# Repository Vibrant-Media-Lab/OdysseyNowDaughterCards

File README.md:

# Odyssey Now Daughter Cards

Replacement daughter card schematics and layouts for the Magnavox Odyssey BLAK version.

## Layout
* `OdysseyDaughterCard<name>` (KiCad 8 project)
  * `3D_models/` (WRL and STEP files for the board)
  * `footprints/` (non-standard footprint libraries for project)
  * `gerbers/` (last generated gerbers for layout)
  * `images/` (a render of the board)
  * `pdf/` (pdfs of schematic and layout)
  * `symbols/` (non-standard symbol libraries for project)
  * `dimensions.txt` (board dimension in meters for easier ordering from places like AllPCB)

## Bill of Materials
* See OdysseyDaughtCardsBillOfMaterials.xlsx for a list components used in the last round of boards made in the VML.

## License
* Designed by Levi Burner and Zachary Horton
* Each card's design is available under Creative Commons Attribution. All license text must be included in any redistribution and attribution must be given to original design and designers. See LICENSE.txt in each card's folder for additional details.

## Old Designs (legacy)
The original git history for each card (including old prototypes that were made and are likely to be floating around in the VML) be found on the `legacy-*` branches.

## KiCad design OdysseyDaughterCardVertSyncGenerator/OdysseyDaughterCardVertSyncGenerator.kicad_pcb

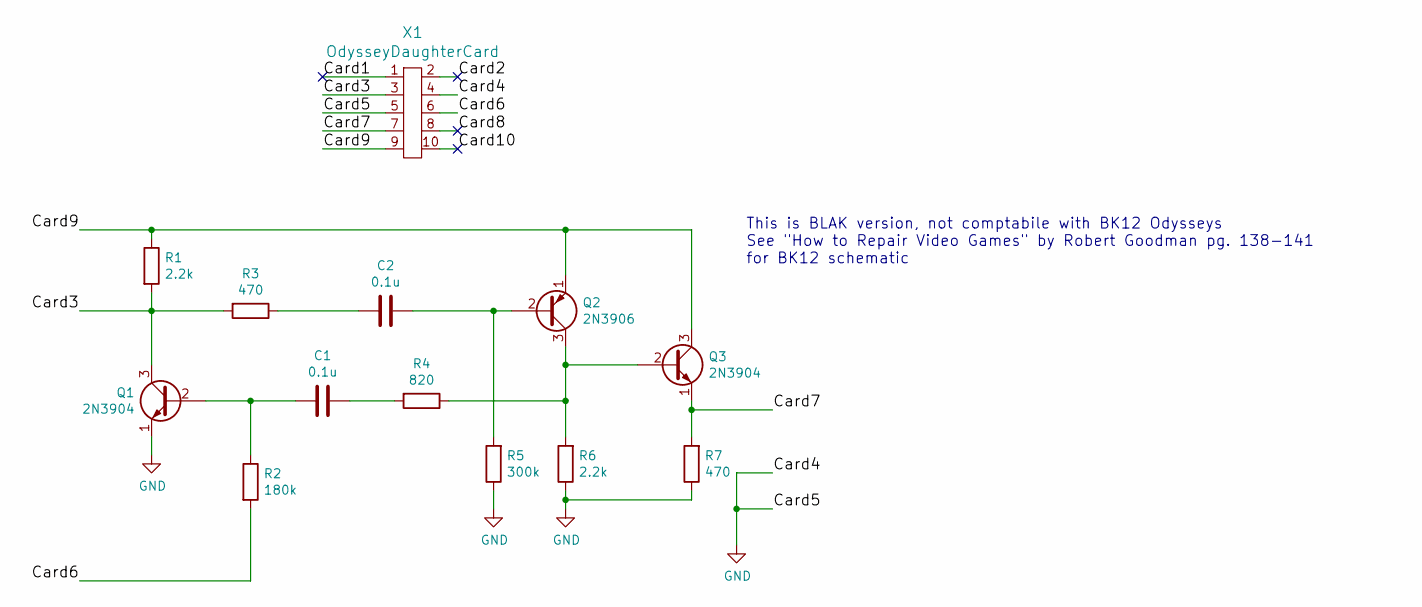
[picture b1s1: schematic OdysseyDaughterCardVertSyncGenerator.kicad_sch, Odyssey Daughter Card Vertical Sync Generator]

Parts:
C1, C2: 0.1u; C_Disc_D5.1mm_W3.2mm_P5.00mm
Q1, Q3: 2N3904; TO-92_Inline_Wide
Q2: 2N3906; TO-92_Inline_Wide
R1, R6: 2.2k; R_Axial_DIN0207_L6.3mm_D2.5mm_P7.62mm_Horizontal
R2: 180k; R_Axial_DIN0207_L6.3mm_D2.5mm_P7.62mm_Horizontal
R3, R7: 470; R_Axial_DIN0207_L6.3mm_D2.5mm_P7.62mm_Horizontal
R4: 820; R_Axial_DIN0207_L6.3mm_D2.5mm_P7.62mm_Horizontal
R5: 300k; R_Axial_DIN0207_L6.3mm_D2.5mm_P7.62mm_Horizontal
X1: OdysseyDaughterCard; Odyssey_Daughter_Card

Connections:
/Card1: X1.1
/Card2: X1.2
/Card3: Q1.3 (C), R1.2, R3.2, X1.3
/Card6: R2.2, X1.6
/Card7: Q3.1 (E), R7.2, X1.7
/Card8: X1.8
/Card9: Q2.1 (E), Q3.3 (C), R1.1, X1.9
/Card10: X1.10
GND: Q1.1 (E), R5.1, R6.1, R7.1, X1.4, X1.5
unnamed: C1.1, R4.2
unnamed: C2.2, R3.1
unnamed: C1.2, Q1.2 (B), R2.1
unnamed: C2.1, Q2.2 (B), R5.2
unnamed: Q2.3 (C), Q3.2 (B), R4.1, R6.2

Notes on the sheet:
This is BLAK version, not comptabile with BK12 Odysseys See "How to Repair Video Games" by Robert Goodman pg. 138-141 for BK12 schematic

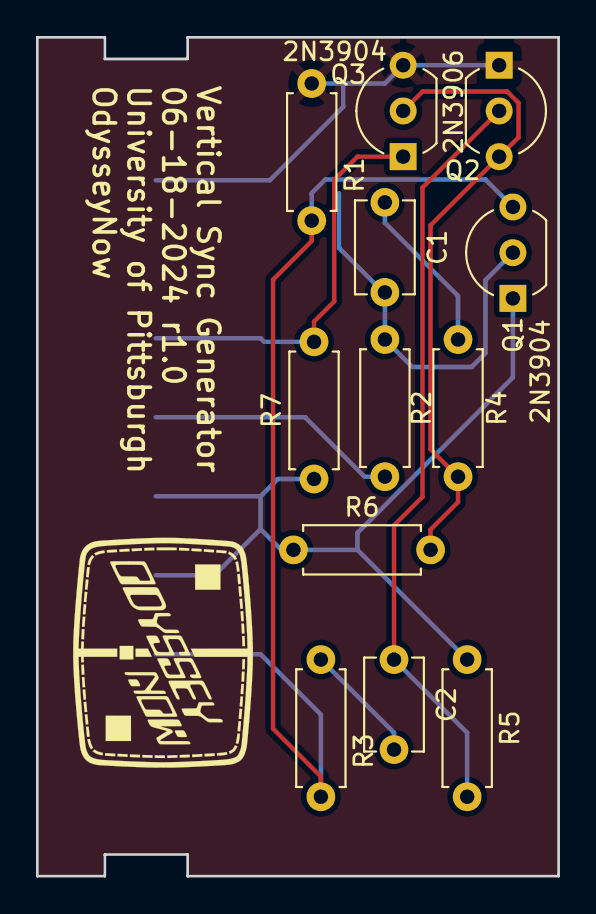
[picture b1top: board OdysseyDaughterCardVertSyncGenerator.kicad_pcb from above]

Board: 2 copper layers, 29.0 x 46.6 mm, 14 parts (0 on the bottom side), 10 nets.

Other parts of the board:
X2: OdysseyNow_Logo; OdysseyNowLogo

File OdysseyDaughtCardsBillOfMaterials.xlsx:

|  |  |  |  |  | # Parts | 19 | 12 | 15 | 19 | 15 | 11
 |  |  |  |  |  | Non PCB Cost Per Unit (10pcs) | 1.6139999999999999 | 2.2650000000000001 | 1.635 | 2.0720000000000001 | 2.0720000000000001 | 1.175
 |  |  |  |  |  | Non PCB Cost Per Unit (100pcs) | 0.8073999999999999 | 1.1888999999999998 | 0.79349999999999987 | 1.0053000000000001 | 1.0926 | 0.54569999999999996
Type | Value | P/N | Link | Notes | CPU (10pcs) | CPU (100pcs) (prices are from 2019) | Flip Flop | Gate Matrix | Horiz Sync Generator | Spot Gen | Summer | Vert Sync Generator
Capacitor | 0.01u | BC2662CT-ND | https://www.digikey.com/product-detail/en/vishay-bc-componen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 |  | 0.11799999999999999 | 5.9900000000000002E-2 |  |  |  | 1
Capacitor | 0.15u | 445-173584-1-ND | https://www.digikey.com/product-detail/en/tdk-corporation/FG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 |  | 0.18 | 0.1021 |  |  |  | 1
Capacitor | 0.1u | BC2665CT-ND | https://www.digikey.com/product-detail/en/vishay-bc-componen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 |  | 0.16 | 8.09E-2 | 2 |  |  | 1 |  | 2
Capacitor | 100p | BC2657CT-ND | https://www.digikey.com/product-detail/en/vishay-bc-componen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 |  | 0.122 | 6.2100000000000002E-2 | 2
Capacitor | 100u | 399-6602-ND | https://www.digikey.com/product-detail/en/kemet/ESK107M6R3AC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 |  | 0.114 | 5.3400000000000003E-2 |  |  | 1
Capacitor | 10u | 399-6597-ND | https://www.digikey.com/product-detail/en/kemet/ESK106M016AC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 |  | 0.105 | 4.9299999999999997E-2 |  |  | 1
Capacitor | 120p | BC2669CT-ND | https://www.digikey.com/product-detail/en/vishay-bc-componen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 |  | 0.12 | 6.08E-2 |  |  |  | 1
Capacitor | 1500p | 445-173589-1-ND | https://www.digikey.com/product-detail/en/tdk-corporation/FG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 |  | 0.18 | 0.1021 |  |  |  | 1
Capacitor | 470p | BC2681CT-ND | https://www.digikey.com/product-detail/en/vishay-bc-componen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 |  | 0.12 | 6.08E-2 |  |  | 1
Capacitor | 680p | BC2690CT-ND | https://www.digikey.com/product-detail/en/vishay-bc-componen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 |  | 0.123 | 6.25E-2 |  |  | 1
Diode | 1N4448 | 1N4448FS-ND | https://www.digikey.com/product-detail/en/on-semiconductor/1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 |  | 8.6999999999999994E-2 | 4.7300000000000002E-2 |  | 3 |  | 2 | 8
Diode | BAT83S | BAT83S-TRGICT-ND | https://www.digikey.com/product-detail/en/vishay-semiconduct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 |  | 0.314 | 0.16639999999999999 |  | 6 |  |  | 4
Inductor | 620uH 9 Ohm | RLB0608-681KL-ND | https://www.digikey.com/product-detail/en/bourns-inc/RLB0608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 |  | 0.314 | 0.16639999999999999 |  |  | 1
Resistor | 470 | CF14JT470RCT-ND | https://www.digikey.com/product-detail/en/stackpole-electron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 |  | 0.04 | 1.6199999999999999E-2 |  |  | 1 |  |  | 2
Resistor | 820 | CF14JT820RCT-ND | https://www.digikey.com/product-detail/en/stackpole-electron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 |  | 0.04 | 1.6199999999999999E-2 |  |  | 1 |  | 1 | 1
Resistor | 100k | CF14JT100KCT-ND | https://www.digikey.com/product-detail/en/stackpole-electron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 |  | 0.04 | 1.6199999999999999E-2 |  |  |  | 1
Resistor | 10k | CF14JT10K0CT-ND | https://www.digikey.com/product-detail/en/stackpole-electron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 |  | 0.04 | 1.6199999999999999E-2 |  |  |  | 5
Resistor | 150k | CF14JT150KCT-ND | https://www.digikey.com/product-detail/en/stackpole-electron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 |  | 0.04 | 1.6199999999999999E-2 |  |  | 1
Resistor | 180k | CF14JT180KCT-ND | https://www.digikey.com/products/en?keywords=CF14JT180KCT-ND |  | 0.04 | 1.6199999999999999E-2 |  |  |  |  |  | 1
Resistor | 18k | CF14JT18K0CT-ND | https://www.digikey.com/product-detail/en/stackpole-electron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 |  | 0.04 | 1.6199999999999999E-2 |  |  |  |  | 1
Resistor | 1k | CF14JT1K00CT-ND | https://www.digikey.com/product-detail/en/stackpole-electron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 |  | 0.04 | 1.6199999999999999E-2 | 2 |  | 2
Resistor | 2.2k | CF14JT2K20CT-ND | https://www.digikey.com/product-detail/en/stackpole-electron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 |  | 0.04 | 1.6199999999999999E-2 | 1 |  |  | 1 |  | 1
Resistor | 270k | CF14JT270KCT-ND | https://www.digikey.com/product-detail/en/stackpole-electron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 |  | 0.04 | 1.6199999999999999E-2 |  |  |  | 1
Resistor | 27k | CF14JT27K0CT-ND | https://www.digikey.com/product-detail/en/stackpole-electron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 |  | 0.04 | 1.6199999999999999E-2 |  |  |  |  | 1
Resistor | 3.3k | CF14JT3K30CT-ND | https://www.digikey.com/product-detail/en/stackpole-electron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 |  | 0.04 | 1.6199999999999999E-2 |  |  | 1
Resistor | 300k | CF14JT300KCT-ND | https://www.digikey.com/product-detail/en/stackpole-electron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 |  | 0.04 | 1.6199999999999999E-2 |  |  | 1 |  |  | 1
Resistor | 4.7k | CF14JT4K70CT-ND | https://www.digikey.com/product-detail/en/stackpole-electron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 |  | 0.04 | 1.6199999999999999E-2 |  | 3
Resistor | 47k | CF14JT47K0CT-ND | https://www.digikey.com/product-detail/en/stackpole-electron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 |  | 0.04 | 1.6199999999999999E-2 | 4
Switch/Button | Slide Switch SPDT Through Hole, Right Angle | CKN9559-ND | https://www.digikey.com/product-detail/en/c-k/OS102011MA1QN1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 |  |  |  | 4
Transistor | 2N3904 | 2N3904FS-ND | https://www.digikey.com/product-detail/en/on-semiconductor/2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 |  | 0.21 | 9.1600000000000001E-2 |  |  | 1 | 3 |  | 2
Transistor | 2N3906 | 2N3906TARFSCT-ND | https://www.digikey.com/product-detail/en/on-semiconductor/2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 |  | 0.19500000000000001 | 0.10349999999999999 | 2 |  |  |  |  | 1
Transistor | BC547B | BC547BTACT-ND | https://www.digikey.com/product-detail/en/on-semiconductor/B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 |  | 0.18099999999999999 | 9.6199999999999994E-2 |  |  | 1
Transistor | BC547C | BC547CBU-ND | https://www.digikey.com/product-detail/en/on-semiconductor/B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 |  | 0.19 | 0.10050000000000001 | 2 |  |  | 1
Transistor | BC556B | BC556BTACT-ND | https://www.digikey.com/product-detail/en/on-semiconductor/B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 |  | 0.188 | 9.9900000000000003E-2 |  |  | 1

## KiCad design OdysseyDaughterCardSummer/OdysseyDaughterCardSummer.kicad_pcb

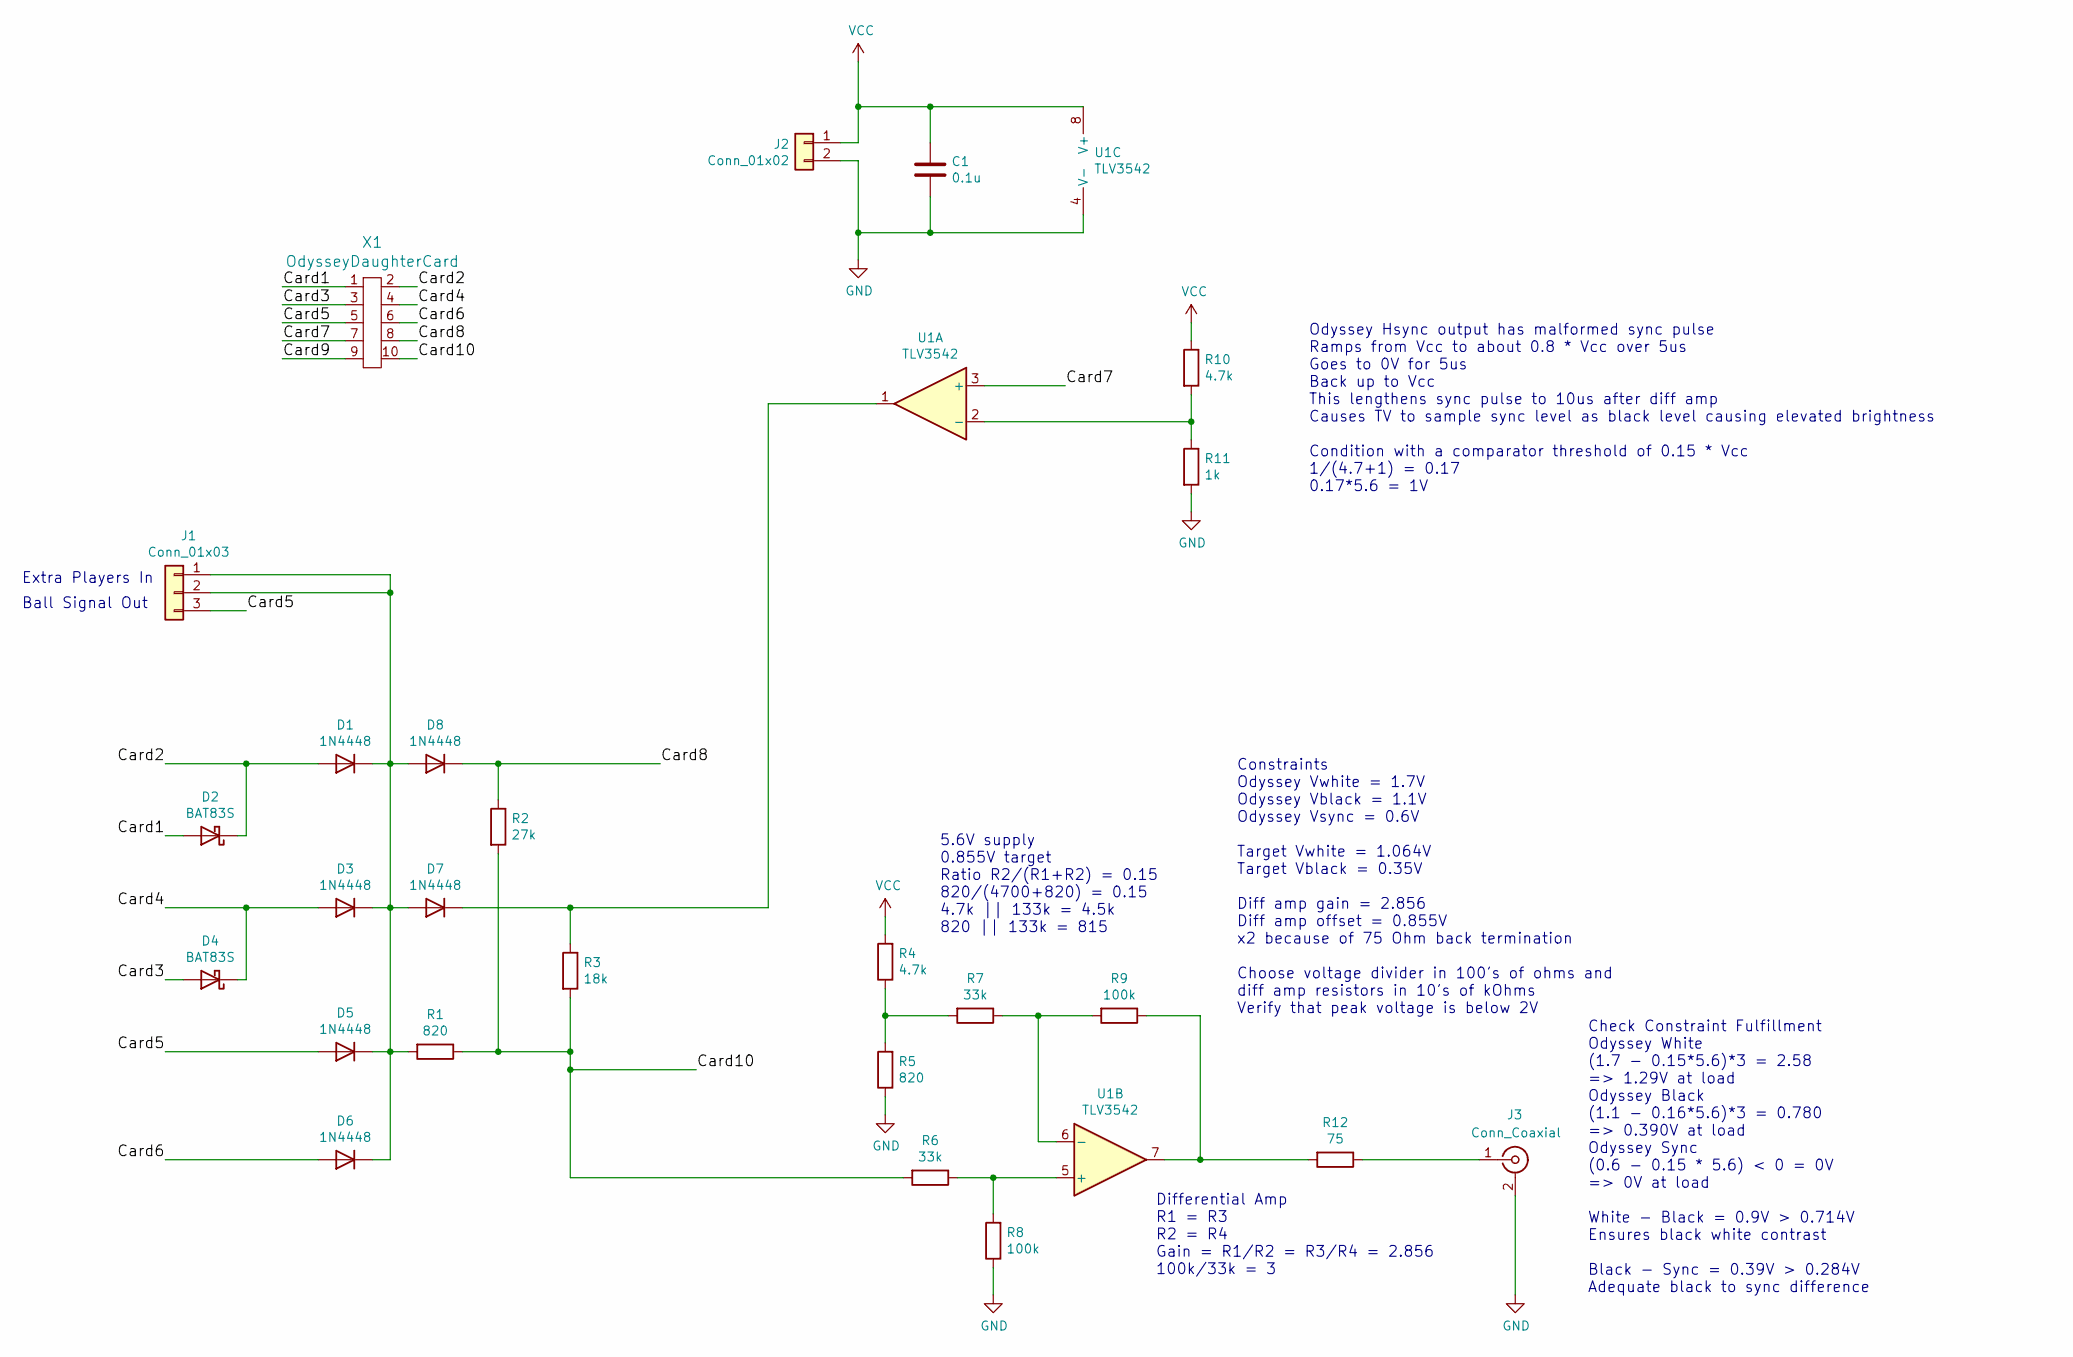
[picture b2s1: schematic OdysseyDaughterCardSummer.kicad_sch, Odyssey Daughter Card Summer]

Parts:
C1: 0.1u; C_Disc_D3.8mm_W2.6mm_P2.50mm
D1, D3, D5, D6, D7, D8: 1N4448; D_DO-35_SOD27_P7.62mm_Horizontal
D2, D4: BAT83S; D_DO-35_SOD27_P7.62mm_Horizontal
J1: Conn_01x03; PinHeader_1x03_P2.54mm_Vertical
J2: Conn_01x02; PinHeader_1x02_P2.54mm_Vertical
J3: Conn_Coaxial; PinHeader_1x02_P2.54mm_Vertical
R1, R5: 820; R_Axial_DIN0207_L6.3mm_D2.5mm_P7.62mm_Horizontal
R2: 27k; R_Axial_DIN0207_L6.3mm_D2.5mm_P7.62mm_Horizontal
R3: 18k; R_Axial_DIN0207_L6.3mm_D2.5mm_P7.62mm_Horizontal
R4, R10: 4.7k; R_Axial_DIN0207_L6.3mm_D2.5mm_P7.62mm_Horizontal
R6, R7: 33k; R_Axial_DIN0207_L6.3mm_D2.5mm_P7.62mm_Horizontal
R8, R9: 100k; R_Axial_DIN0207_L6.3mm_D2.5mm_P7.62mm_Horizontal
R11: 1k; R_Axial_DIN0207_L6.3mm_D2.5mm_P7.62mm_Horizontal
R12: 75; R_Axial_DIN0207_L6.3mm_D2.5mm_P7.62mm_Horizontal
U1: TLV3542; SOIC-8_3.9x4.9mm_P1.27mm
X1: OdysseyDaughterCard; Odyssey_Daughter_Card

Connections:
/Card1: D2.2 (A), X1.1
/Card2: D1.2 (A), D2.1 (K), X1.2
/Card3: D4.2 (A), X1.3
/Card4: D3.2 (A), D4.1 (K), X1.4
/Card5: D5.2 (A), J1.3, X1.5
/Card6: D6.2 (A), X1.6
/Card7: U1.3 (+), X1.7
/Card8: D8.1 (K), R2.1, X1.8
/Card9: X1.9
/Card10: R1.1, R2.2, R3.2, R6.2, X1.10
GND: C1.2, J2.2, J3.2 (Ext), R5.1, R8.1, R11.2, U1.4 (V-)
unnamed: D1.1 (K), D3.1 (K), D5.1 (K), D6.1 (K), D7.2 (A), D8.2 (A), J1.1, J1.2, R1.2
unnamed: D7.1 (K), R3.1, U1.1
unnamed: J3.1 (In), R12.1
unnamed: R4.1, R5.2, R7.2
unnamed: R9.1, R12.2, U1.7
unnamed: R10.2, R11.1, U1.2 (-)
unnamed: R6.1, R8.2, U1.5 (+)
unnamed: R7.1, R9.2, U1.6 (-)
VCC: C1.1, J2.1, R4.2, R10.1, U1.8 (V+)

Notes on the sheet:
Odyssey Hsync output has malformed sync pulse Ramps from Vcc to about 0.8 * Vcc over 5us Goes to 0V for 5us Back up to Vcc This lengthens sync pulse to 10us after diff amp Causes TV to sample sync level as black level causing elevated brightness Condition with a comparator threshold of 0.15 * Vcc 1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
Check Constraint Fulfillment Odyssey White (1.7 - 0.15*5.6)*3 = 2.58 => 1.29V at load Odyssey Black (1.1 - 0.16*5.6)*3 = 0.780 => 0.390V at load Odyssey Sync (0.6 - 0.15 * 5.6) < 0 = 0V => 0V at load White - Black = 0.9V > 0.714V Ensures black white contrast Black - Sync = 0.39V > 0.284V Adequate b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
Differential Amp R1 = R3 R2 = R4 Gain = R1/R2 = R3/R4 = 2.856 100k/33k = 3
Constraints Odyssey Vwhite = 1.7V Odyssey Vblack = 1.1V Odyssey Vsync = 0.6V Target Vwhite = 1.064V Target Vblack = 0.35V Diff amp gain = 2.856 Diff amp offset = 0.855V x2 because of 75 Ohm back termination Choose voltage divider in 100's of ohms and diff amp resistors in 10's of kOhms Verify that 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
5.6V supply 0.855V target Ratio R2/(R1+R2) = 0.15 820/(4700+820) = 0.15 4.7k || 133k = 4.5k 820 || 133k = 815
Extra Players In
Ball Signal Out

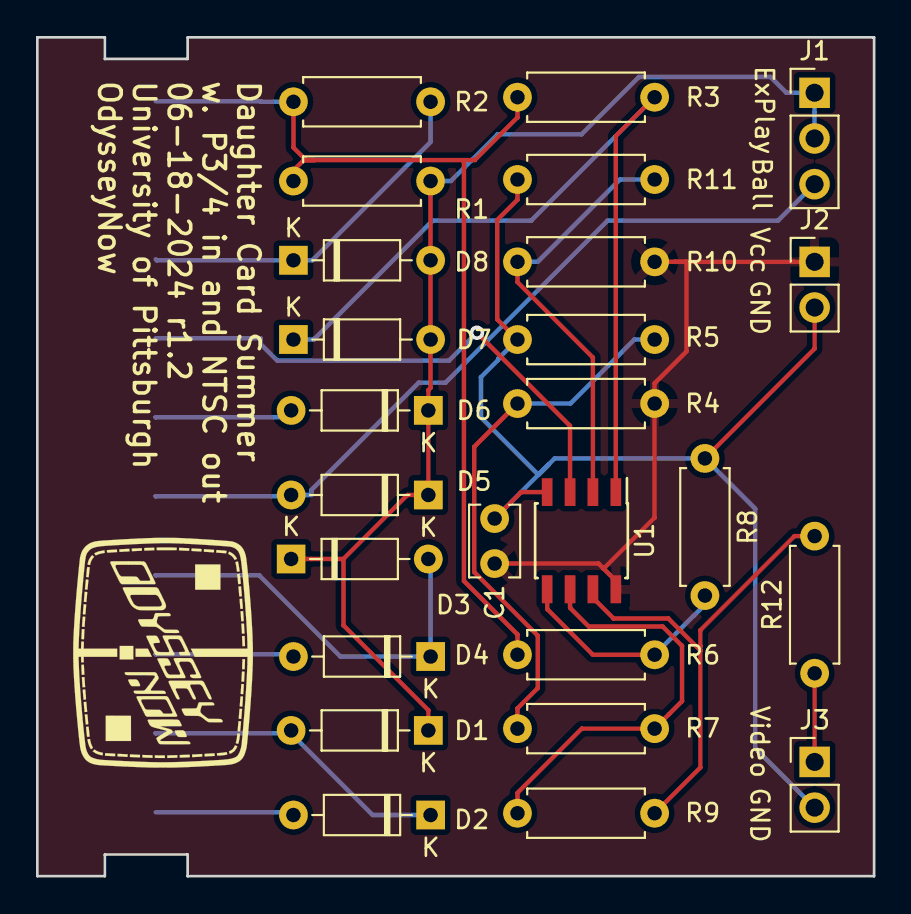
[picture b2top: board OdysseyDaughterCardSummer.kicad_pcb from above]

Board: 2 copper layers, 46.5 x 46.6 mm, 27 parts (0 on the bottom side), 19 nets.

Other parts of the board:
X2: OdysseyNow_Logo; OdysseyNowLogo

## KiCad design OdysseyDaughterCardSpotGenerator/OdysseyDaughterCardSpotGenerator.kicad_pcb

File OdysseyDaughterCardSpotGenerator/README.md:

# Odyssey Restoration Project Card Template

This is a KiCad template for an Odyssey Daughter Card.

## Revisions

### 0.1 5-29-18
Initial Version

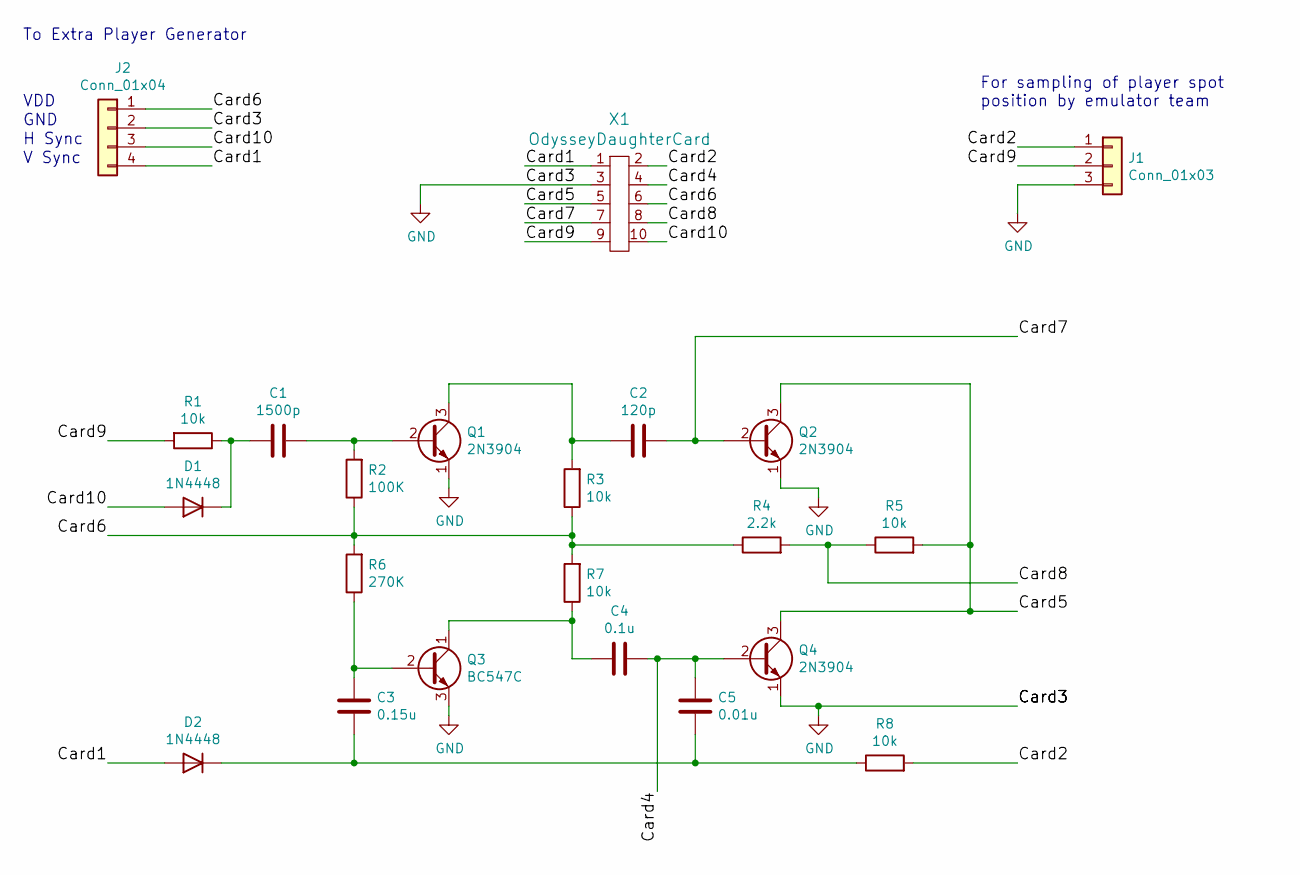
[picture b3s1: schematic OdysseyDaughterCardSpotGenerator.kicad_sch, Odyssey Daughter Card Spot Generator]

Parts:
C1: 1500p; C_Rect_L4.0mm_W2.5mm_P2.50mm
C2: 120p; C_Rect_L4.0mm_W2.5mm_P2.50mm
C3: 0.15u; C_Rect_L4.6mm_W5.5mm_P2.50mm_MKS02_FKP02
C4: 0.1u; C_Rect_L4.0mm_W2.5mm_P2.50mm
C5: 0.01u; C_Rect_L4.0mm_W2.5mm_P2.50mm
D1, D2: 1N4448; D_DO-35_SOD27_P7.62mm_Horizontal
J1: Conn_01x03; PinHeader_1x03_P2.54mm_Vertical
J2: Conn_01x04; PinHeader_1x04_P2.54mm_Vertical
Q1, Q2, Q4: 2N3904; TO-92_Inline_Wide
Q3: BC547C; TO-92_Inline_Wide
R1, R3, R5, R7, R8: 10k; R_Axial_DIN0207_L6.3mm_D2.5mm_P7.62mm_Horizontal
R2: 100K; R_Axial_DIN0207_L6.3mm_D2.5mm_P7.62mm_Horizontal
R4: 2.2k; R_Axial_DIN0207_L6.3mm_D2.5mm_P7.62mm_Horizontal
R6: 270K; R_Axial_DIN0207_L6.3mm_D2.5mm_P7.62mm_Horizontal
X1: OdysseyDaughterCard; Odyssey_Daughter_Card

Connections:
/Card1: D2.2 (A), J2.4, X1.1
/Card2: J1.1, R8.2, X1.2
/Card4: C4.2, C5.1, Q4.2 (B), X1.4
/Card5: Q2.3 (C), Q4.3 (C), R5.2, X1.5
/Card6: J2.1, R2.1, R3.1, R4.1, R6.2, R7.2, X1.6
/Card7: C2.1, Q2.2 (B), X1.7
/Card8: R4.2, R5.1, X1.8
/Card9: J1.2, R1.2, X1.9
/Card10: D1.2 (A), J2.3, X1.10
GND: J1.3, J2.2, Q1.1 (E), Q2.1 (E), Q3.3 (E), Q4.1 (E), X1.3
unnamed: C1.2, D1.1 (K), R1.1
unnamed: C3.1, C5.2, D2.1 (K), R8.1
unnamed: C1.1, Q1.2 (B), R2.2
unnamed: C2.2, Q1.3 (C), R3.2
unnamed: C3.2, Q3.2 (B), R6.1
unnamed: C4.1, Q3.1 (C), R7.1

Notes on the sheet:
VDD
For sampling of player spot position by emulator team
H Sync
GND
To Extra Player Generator
V Sync

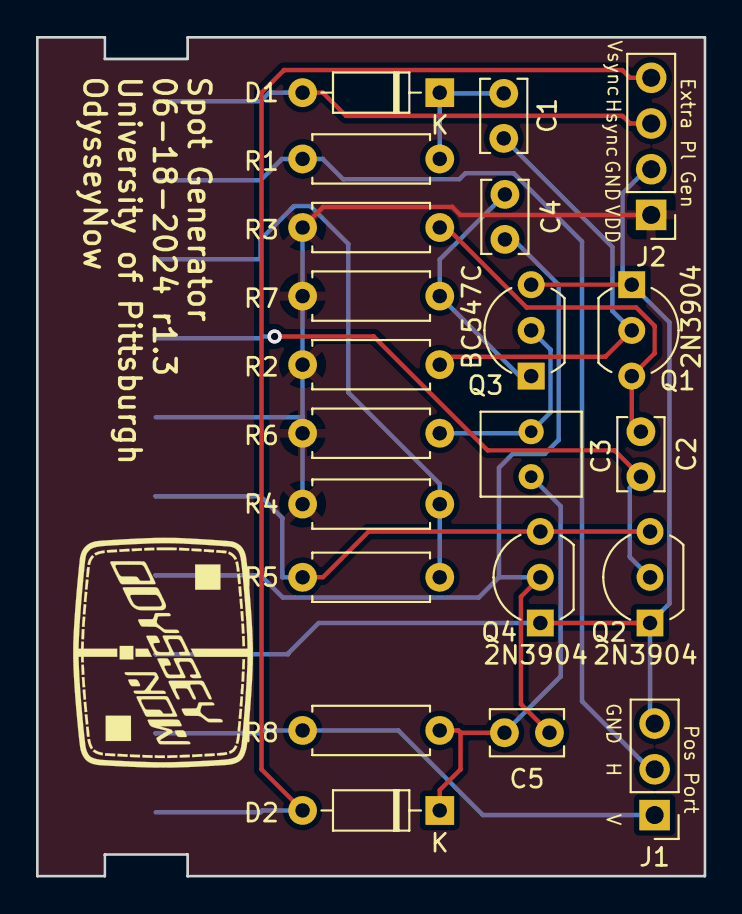
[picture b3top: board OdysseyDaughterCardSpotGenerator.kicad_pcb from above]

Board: 2 copper layers, 37.1 x 46.6 mm, 23 parts (0 on the bottom side), 16 nets.

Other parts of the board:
X2: OdysseyNow_Logo; OdysseyNowLogo

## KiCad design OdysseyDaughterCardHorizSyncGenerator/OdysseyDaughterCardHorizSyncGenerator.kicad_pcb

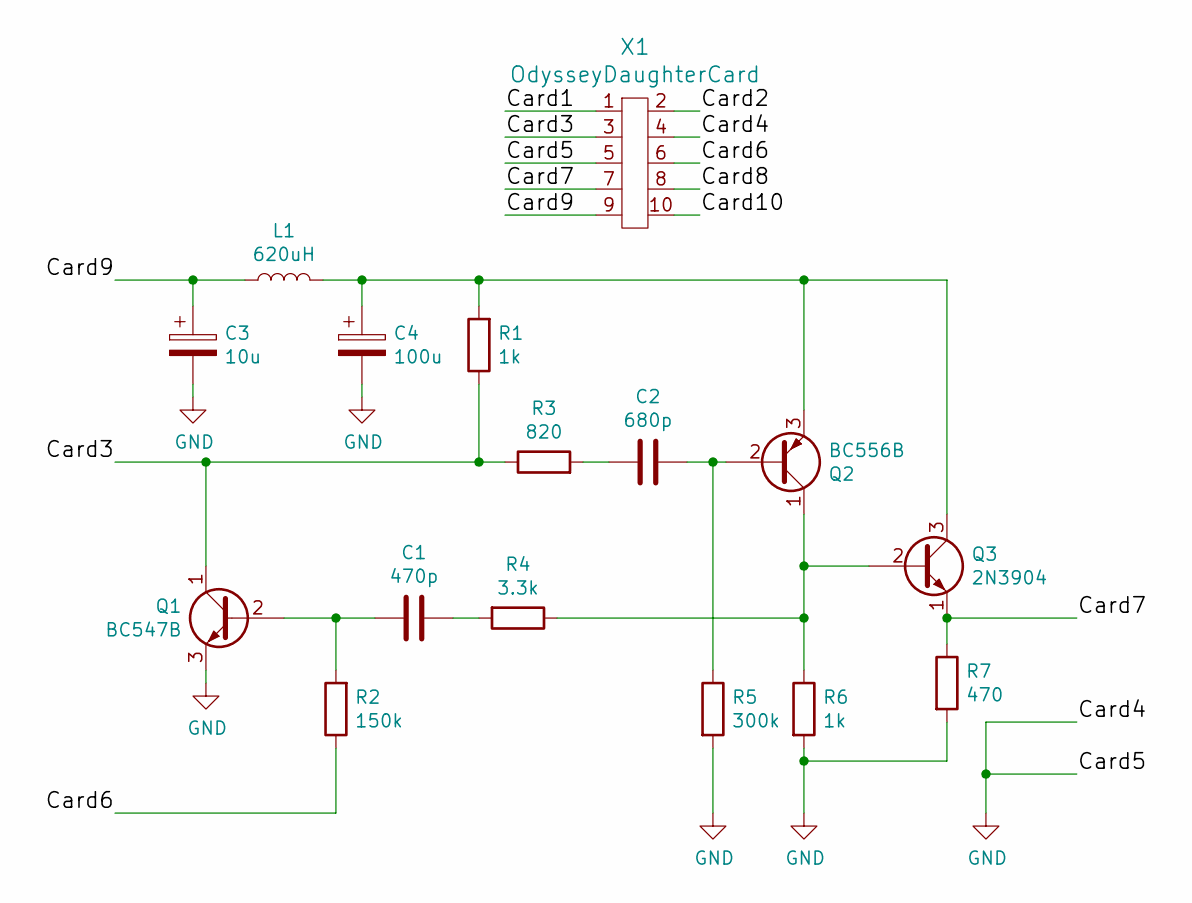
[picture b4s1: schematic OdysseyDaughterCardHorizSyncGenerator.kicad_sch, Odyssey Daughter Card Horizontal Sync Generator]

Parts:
C1: 470p; C_Disc_D5.1mm_W3.2mm_P5.00mm
C2: 680p; C_Disc_D5.1mm_W3.2mm_P5.00mm
C3: 10u; CP_Radial_D5.0mm_P2.00mm
C4: 100u; CP_Radial_D5.0mm_P2.00mm
L1: 620uH; L_Radial_D7.0mm_P3.00mm
Q1: BC547B; TO-92_Inline_Wide
Q2: BC556B; TO-92_Inline_Wide
Q3: 2N3904; TO-92_Inline_Wide
R1, R6: 1k; R_Axial_DIN0207_L6.3mm_D2.5mm_P7.62mm_Horizontal
R2: 150k; R_Axial_DIN0207_L6.3mm_D2.5mm_P7.62mm_Horizontal
R3: 820; R_Axial_DIN0207_L6.3mm_D2.5mm_P7.62mm_Horizontal
R4: 3.3k; R_Axial_DIN0207_L6.3mm_D2.5mm_P7.62mm_Horizontal
R5: 300k; R_Axial_DIN0207_L6.3mm_D2.5mm_P7.62mm_Horizontal
R7: 470; R_Axial_DIN0207_L6.3mm_D2.5mm_P7.62mm_Horizontal
X1: OdysseyDaughterCard; Odyssey_Daughter_Card

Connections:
/Card1: X1.1
/Card2: X1.2
/Card3: Q1.1 (C), R1.1, R3.1, X1.3
/Card6: R2.1, X1.6
/Card7: Q3.1 (E), R7.1, X1.7
/Card8: X1.8
/Card9: C3.1, L1.1, X1.9
/Card10: X1.10
GND: C3.2, C4.2, Q1.3 (E), R5.2, R6.2, R7.2, X1.4, X1.5
unnamed: C1.1, R4.2
unnamed: C2.2, R3.2
unnamed: C1.2, Q1.2 (B), R2.2
unnamed: C2.1, Q2.2 (B), R5.1
unnamed: Q2.1 (C), Q3.2 (B), R4.1, R6.1
unnamed: C4.1, L1.2, Q2.3 (E), Q3.3 (C), R1.2

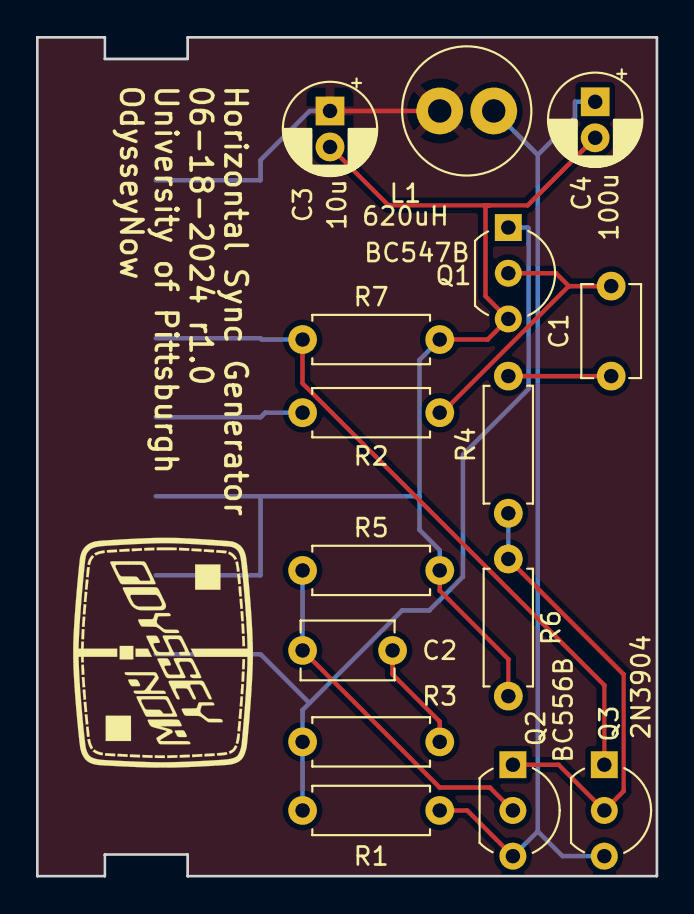
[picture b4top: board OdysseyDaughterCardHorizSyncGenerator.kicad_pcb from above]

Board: 2 copper layers, 34.4 x 46.6 mm, 17 parts (0 on the bottom side), 11 nets.

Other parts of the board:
X1#2: OdysseyNow_Logo; OdysseyNowLogo

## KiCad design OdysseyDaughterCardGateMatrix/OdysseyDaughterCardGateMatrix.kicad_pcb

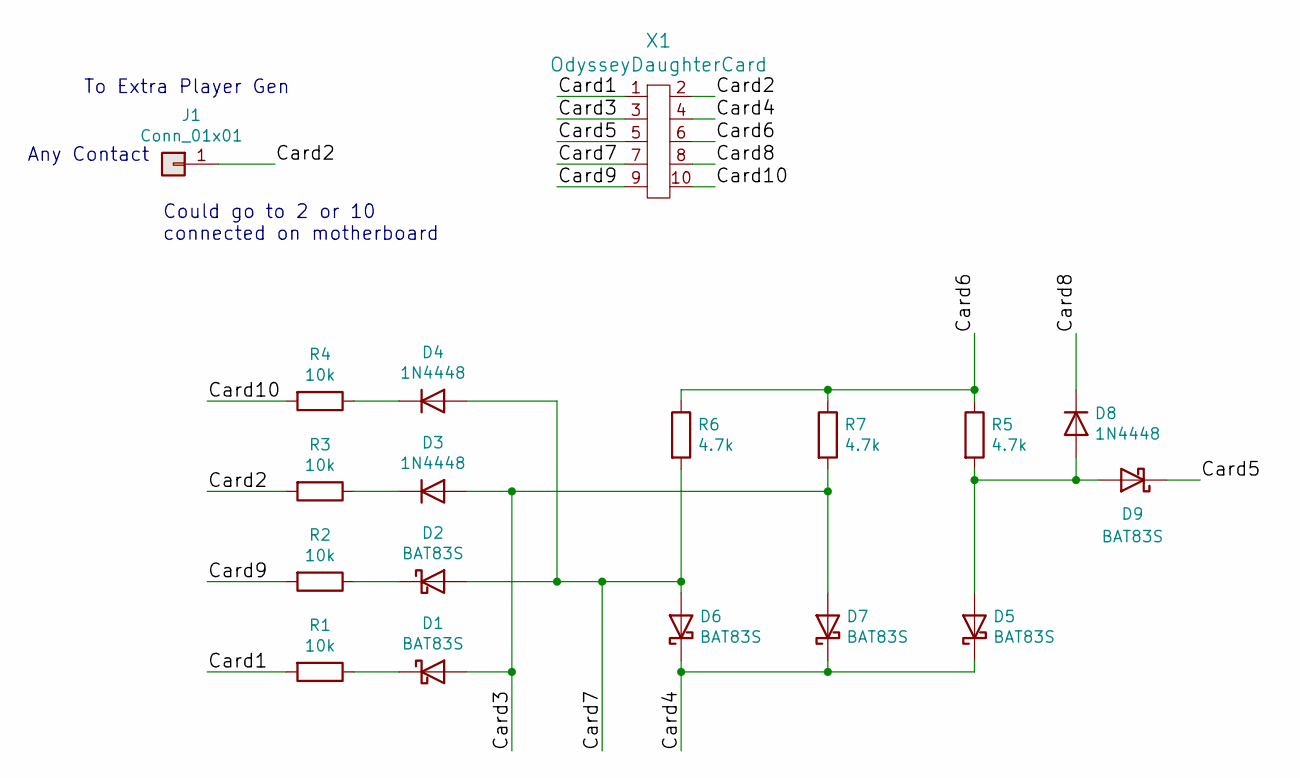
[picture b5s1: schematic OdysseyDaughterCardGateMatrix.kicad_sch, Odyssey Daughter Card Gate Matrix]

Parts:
D1, D2, D5, D6, D7, D9: BAT83S; D_DO-41_SOD81_P7.62mm_Horizontal
D3, D4, D8: 1N4448; D_DO-35_SOD27_P7.62mm_Horizontal
J1: Conn_01x01; PinHeader_1x01_P2.54mm_Vertical
R1, R2, R3, R4: 10k; R_Axial_DIN0207_L6.3mm_D2.5mm_P7.62mm_Horizontal
R5, R6, R7: 4.7k; R_Axial_DIN0207_L6.3mm_D2.5mm_P7.62mm_Horizontal
X1: OdysseyDaughterCard; Odyssey_Daughter_Card

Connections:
/Card1: R1.2, X1.1
/Card2: J1.1, R3.2, X1.2
/Card3: D1.2 (A), D3.2 (A), D7.2 (A), R7.2, X1.3
/Card4: D5.1 (K), D6.1 (K), D7.1 (K), X1.4
/Card5: D9.1 (K), X1.5
/Card6: R5.1, R6.1, R7.1, X1.6
/Card7: D2.2 (A), D4.2 (A), D6.2 (A), R6.2, X1.7
/Card8: D8.1 (K), X1.8
/Card9: R2.2, X1.9
/Card10: R4.2, X1.10
unnamed: D1.1 (K), R1.1
unnamed: D2.1 (K), R2.1
unnamed: D3.1 (K), R3.1
unnamed: D4.1 (K), R4.1
unnamed: D5.2 (A), D8.2 (A), D9.2 (A), R5.2

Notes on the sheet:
Could go to 2 or 10 connected on motherboard
To Extra Player Gen
Any Contact

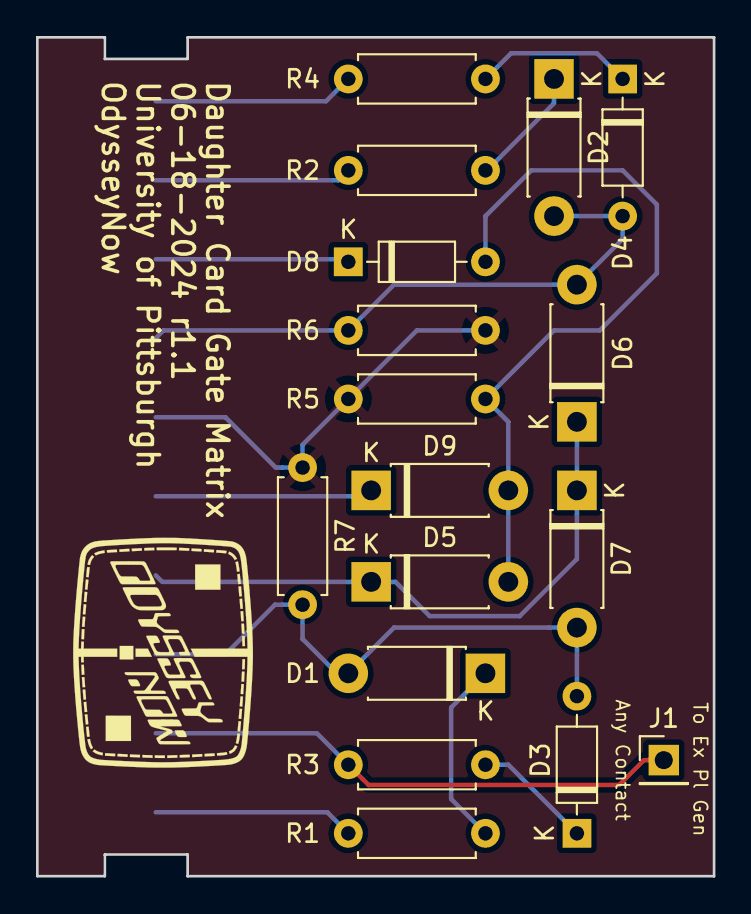
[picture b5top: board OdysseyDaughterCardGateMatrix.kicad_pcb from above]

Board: 2 copper layers, 37.6 x 46.6 mm, 19 parts (0 on the bottom side), 15 nets.

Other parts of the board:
X1#2: OdysseyNow_Logo; OdysseyNowLogo

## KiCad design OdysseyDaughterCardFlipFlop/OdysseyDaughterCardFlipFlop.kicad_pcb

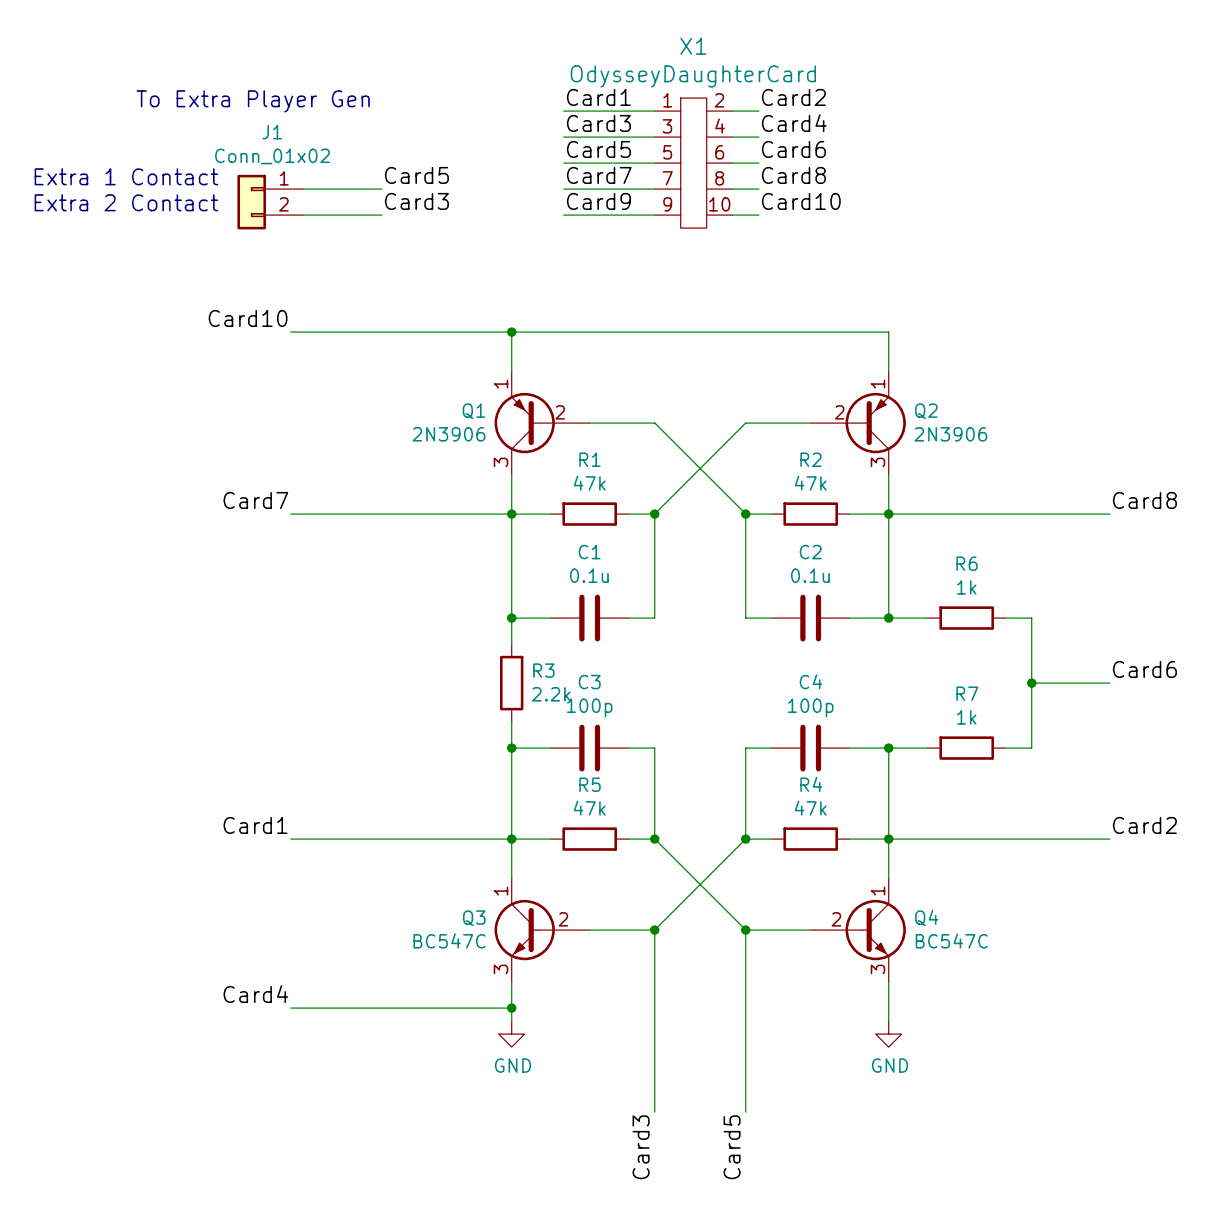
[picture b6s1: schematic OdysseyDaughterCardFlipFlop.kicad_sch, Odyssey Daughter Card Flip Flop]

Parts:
C1, C2: 0.1u; C_Disc_D5.1mm_W3.2mm_P5.00mm
C3, C4: 100p; C_Disc_D5.1mm_W3.2mm_P5.00mm
J1: Conn_01x02; PinHeader_1x02_P2.54mm_Vertical
Q1, Q2: 2N3906; TO-92_Inline_Wide
Q3, Q4: BC547C; TO-92_Inline_Wide
R1, R2, R4, R5: 47k; R_Axial_DIN0207_L6.3mm_D2.5mm_P7.62mm_Horizontal
R3: 2.2k; R_Axial_DIN0207_L6.3mm_D2.5mm_P7.62mm_Horizontal
R6, R7: 1k; R_Axial_DIN0207_L6.3mm_D2.5mm_P7.62mm_Horizontal
X1: OdysseyDaughterCard; Odyssey_Daughter_Card

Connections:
/Card1: C3.2, Q3.1 (C), R3.1, R5.1, X1.1
/Card2: C4.1, Q4.1 (C), R4.1, R7.2, X1.2
/Card3: C4.2, J1.2, Q3.2 (B), R4.2, X1.3
/Card5: C3.1, J1.1, Q4.2 (B), R5.2, X1.5
/Card6: R6.1, R7.1, X1.6
/Card7: C1.2, Q1.3 (C), R1.2, R3.2, X1.7
/Card8: C2.1, Q2.3 (C), R2.1, R6.2, X1.8
/Card9: X1.9
/Card10: Q1.1 (E), Q2.1 (E), X1.10
GND: Q3.3 (E), Q4.3 (E), X1.4
unnamed: C2.2, Q1.2 (B), R2.2
unnamed: C1.1, Q2.2 (B), R1.1

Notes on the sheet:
To Extra Player Gen
Extra 2 Contact
Extra 1 Contact

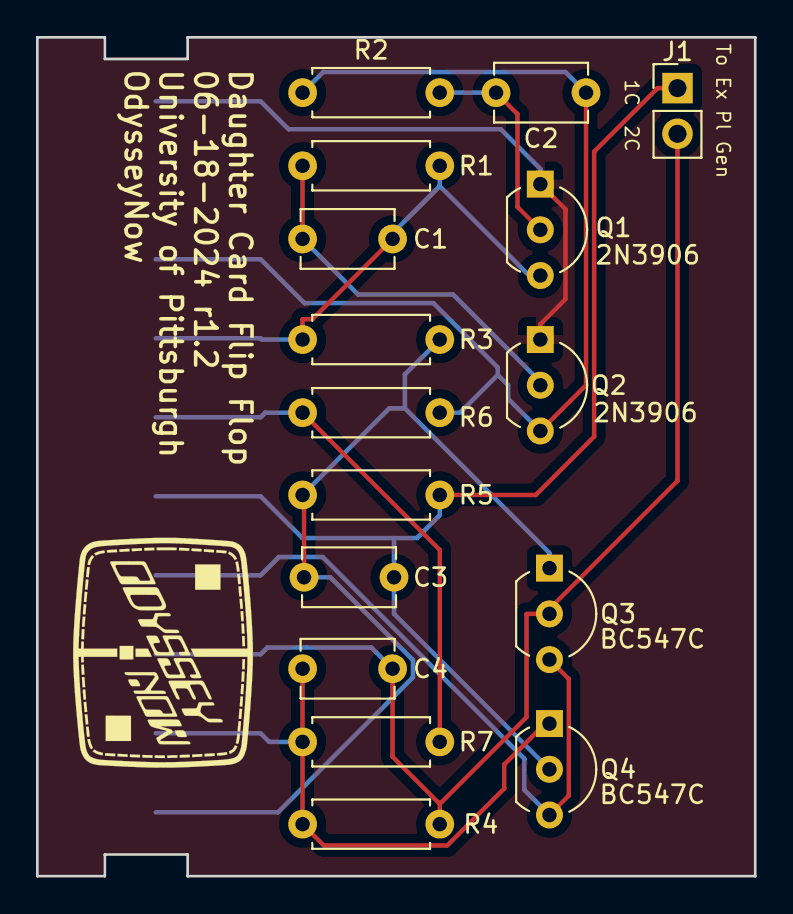
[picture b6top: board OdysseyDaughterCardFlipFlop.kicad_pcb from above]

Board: 2 copper layers, 39.9 x 46.6 mm, 18 parts (0 on the bottom side), 11 nets.

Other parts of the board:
X1#2: OdysseyNow_Logo; OdysseyNowLogo
